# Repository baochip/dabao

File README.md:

# Dabao board design files

This repo contains the Kicad design files for the Dabao evaluation board for the Baochip-1x.

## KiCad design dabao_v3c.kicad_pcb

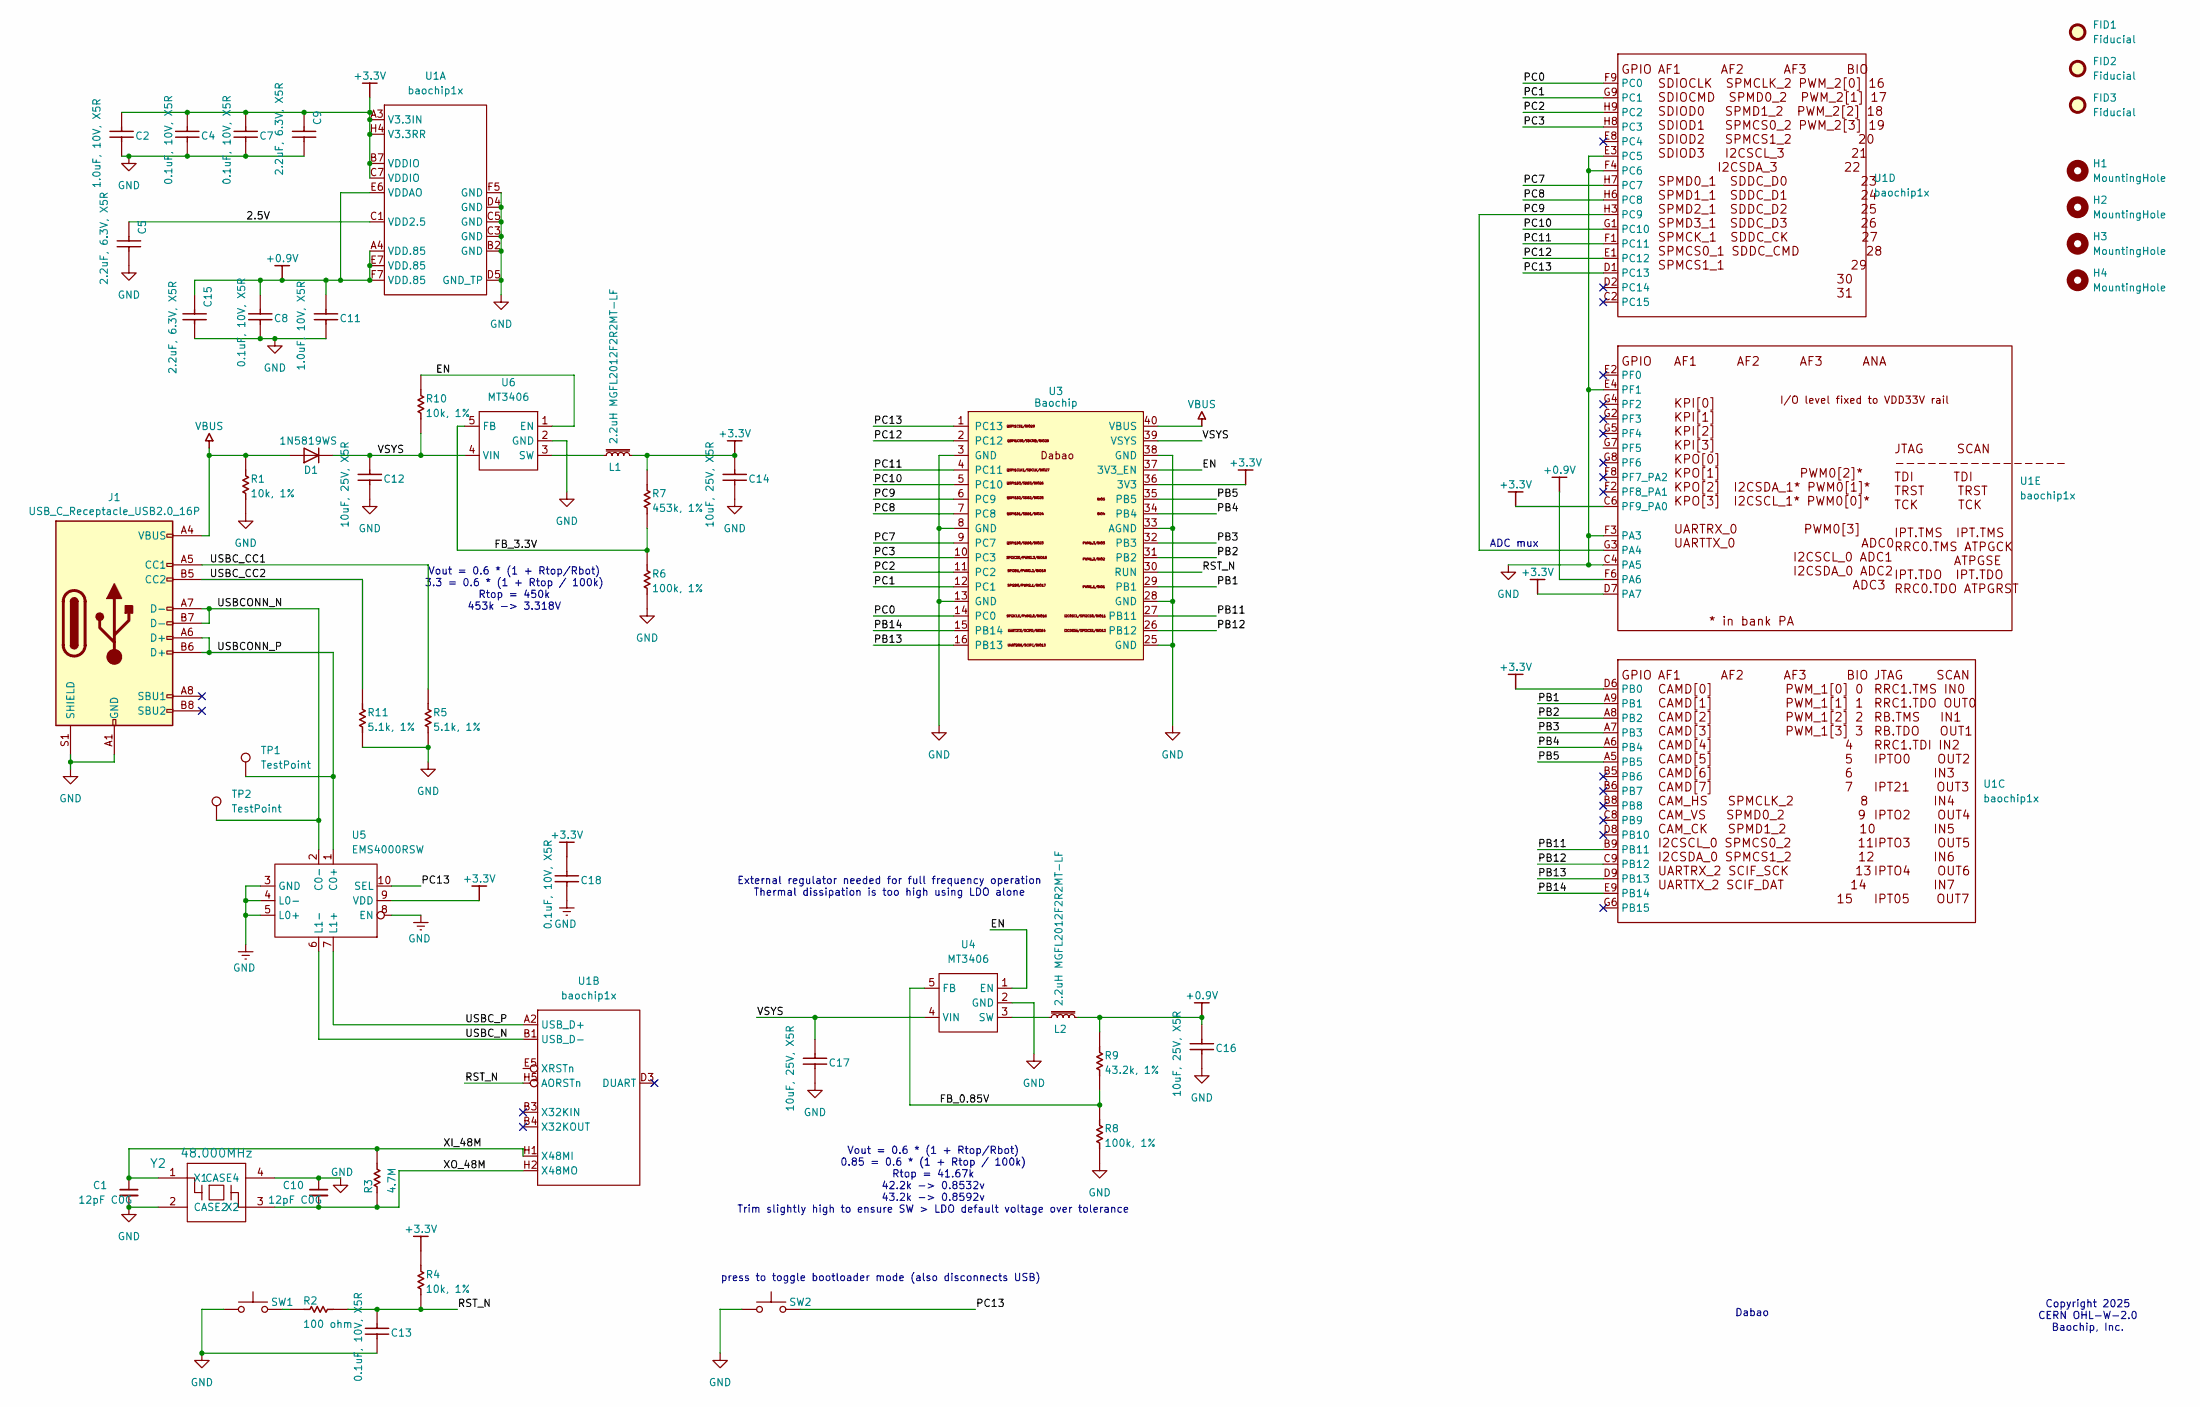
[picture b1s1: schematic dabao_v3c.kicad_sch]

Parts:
C1, C10: 12pF C0G; C_0201_0603Metric; Rating C0G 50V 0603; MPN CC0201JRNPO9BN120; LCSC C277478
C2, C11: 1.0uF, 10V, X5R; C_0201_0603Metric; MPN CL05A105KA5NQNC; LCSC C76935
C4, C7, C8, C13, C18: 0.1uF, 10V, X5R; C_0201_0603Metric; MPN CL05B104KO5NNNC; LCSC C76934
C5, C9, C15: 2.2uF, 6.3V, X5R; C_0201_0603Metric; MPN GRM033R60J225ME47D; LCSC C76933
C12, C14, C16, C17: 10uF, 25V, X5R; C_0603_1608Metric; MPN CL10A106MA8NRNC; LCSC C96446
D1: 1N5819WS; D_SOD-323; MPN SD103AWS; LCSC C191023
FID1, FID2: Fiducial; IRIS fiducial 0.4mm
FID3: Fiducial; IRIS fiducial2 0.4mm
H1, H2, H3, H4: MountingHole; MountingHole_2.2mm_M2_DIN965
J1: USB_C_Receptacle_USB2.0_16P; USB_C_Receptacle_HRO_TYPE-C-31-M-12; LCSC C165948
L1, L2: 2.2uH MGFL2012F2R2MT-LF; L_0805_2012Metric; LCSC C281115
R1, R4, R10: 10k, 1%; R_0201_0603Metric; MPN ANY; LCSC C106225
R2: 100 ohm; R_0402_1005Metric; MPN ANY; LCSC C106232
R3: 4.7M; R_0402_1005Metric; MPN ANY; LCSC C474132
R5, R11: 5.1k, 1%; R_0402_1005Metric; MPN ANY; LCSC C25905
R6, R8: 100k, 1%; R_0201_0603Metric; MPN ANY; LCSC C106224
R7: 453k, 1%; R_0201_0603Metric; MPN ANY; LCSC C423509
R9: 43.2k, 1%; R_0201_0603Metric; MPN ANY; LCSC C158519
SW1, SW2: SW_Push; SW_Push_1P1T_XKB_TS-1187A; MPN TS-1187A-B-B-B; LCSC C528026
TP1, TP2: TestPoint; TestPoint_Pad_D1.0mm
U1: baochip1x; WLCSP-71_9x8_4.062x3.762mm
U3: Baochip; Dabao_Vendor_Substrate
U4, U6: MT3406; SOT-23-5; LCSC C22462728
U5: EMS4000RSW; QFN-10_1.4x1.8_Pitch0.4mm; LCSC C49186227
Y2: 48.000MHz; Crystal_SMD_3225-4Pin_3.2x2.5mm; LCSC C2892060

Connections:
+0.9V: C8.1, C11.1, C15.1, C16.1, L2.2, R9.1, U1.A4 (VDD.85), U1.E6 (VDDAO), U1.E7 (VDD.85), U1.F6 (PA6), U1.F7 (VDD.85)
+3.3V: C2.1, C4.1, C7.1, C9.1, C14.1, C18.1, L1.2, R4.1, R7.1, U1.A3 (V3.3IN), U1.B7 (VDDIO), U1.C6 (PF9_PA0), U1.C7 (VDDIO), U1.D6 (PB0), U1.D7 (PA7), U1.H4 (V3.3RR), U3.36 (3V3), U5.9 (VDD)
/2.5V: C5.1, U1.C1 (VDD2.5)
/EN: R10.1, U3.37 (3V3_EN), U4.1 (EN), U6.1 (EN)
/FB_0.85V: R8.1, R9.2, U4.5 (FB)
/FB_3.3V: R6.1, R7.2, U6.5 (FB)
/PB1: U1.A9 (PB1), U3.29 (PB1)
/PB2: U1.A8 (PB2), U3.31 (PB2)
/PB3: U1.A7 (PB3), U3.32 (PB3)
/PB4: U1.A6 (PB4), U3.34 (PB4)
/PB5: U1.A5 (PB5), U3.35 (PB5)
/PB11: U1.B9 (PB11), U3.27 (PB11)
/PB12: U1.C9 (PB12), U3.26 (PB12)
/PB13: U1.D9 (PB13), U3.16 (PB13)
/PB14: U1.E9 (PB14), U3.15 (PB14)
/PC0: U1.F9 (PC0), U3.14 (PC0)
/PC1: U1.G9 (PC1), U3.12 (PC1)
/PC2: U1.H9 (PC2), U3.11 (PC2)
/PC3: U1.H8 (PC3), U3.10 (PC3)
/PC7: U1.H7 (PC7), U3.9 (PC7)
/PC8: U1.H6 (PC8), U3.7 (PC8)
/PC9: U1.G3 (PA4), U1.H3 (PC9), U3.6 (PC9)
/PC10: U1.G1 (PC10), U3.5 (PC10)
/PC11: U1.F1 (PC11), U3.4 (PC11)
/PC12: U1.E1 (PC12), U3.2 (PC12)
/PC13: SW2.2, U1.D1 (PC13), U3.1 (PC13), U5.10 (SEL)
/RST_N: C13.1, R2.2, R4.2, U1.H5 (AORSTn), U3.30 (RUN)
/USBCONN_N: J1.A7 (D-), J1.B7 (D-), TP2.1, U5.2 (C0-)
/USBCONN_P: J1.A6 (D+), J1.B6 (D+), TP1.1, U5.1 (C0+)
/USBC_CC1: J1.A5 (CC1), R5.2
/USBC_CC2: J1.B5 (CC2), R11.2
/USBC_N: U1.B1 (USB_D-), U5.6 (L1-)
/USBC_P: U1.A2 (USB_D+), U5.7 (L1+)
/VSYS: C12.1, C17.1, D1.1 (K), R10.2, U3.39 (VSYS), U4.4 (VIN), U6.4 (VIN)
/XI_48M: C1.1, R3.2, U1.H1 (X48MI), Y2.1 (X1)
/XO_48M: C10.2, R3.1, U1.H2 (X48MO), Y2.3 (X2)
GND: C1.2, C2.2, C4.2, C5.2, C7.2, C8.2, C9.2, C10.1, C11.2, C12.2, C13.2, C14.2, C15.2, C16.2, C17.2, C18.2, J1.A1 (GND), J1.A12 (GND), J1.B1 (GND), J1.B12 (GND), J1.S1 (SHIELD), R1.2, R5.1, R6.2, R8.2, R11.1, SW1.1, SW2.1, U1.B2 (GND), U1.C3 (GND), U1.C4 (PA5), U1.C5 (GND), U1.D4 (GND), U1.D5 (GND_TP), U1.E3 (PC5), U1.E4 (PF1), U1.F3 (PA3), U1.F4 (PC6), U1.F5 (GND), U3.3 (GND), U3.8 (GND), U3.13 (GND), U3.25 (GND), U3.28 (GND), U3.33 (AGND), U3.38 (GND), U4.2 (GND), U5.3 (GND), U5.4 (L0-), U5.5 (L0+), U5.8 (EN), U6.2 (GND), Y2.2 (CASE2), Y2.4 (CASE4)
unnamed: R2.1, SW1.2
unnamed: L2.1, U4.3 (SW)
unnamed: L1.1, U6.3 (SW)
VBUS: D1.2 (A), J1.A4 (VBUS), J1.A9 (VBUS), J1.B4 (VBUS), J1.B9 (VBUS), R1.1, U3.40 (VBUS)

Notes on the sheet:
Vout = 0.6 * (1 + Rtop/Rbot) 3.3 = 0.6 * (1 + Rtop / 100k) Rtop = 450k 453k -> 3.318V
ADC mux
External regulator needed for full frequency operation Thermal dissipation is too high using LDO alone
Copyright 2025 CERN OHL-W-2.0 Baochip, Inc.
Dabao
press to toggle bootloader mode (also disconnects USB)
Vout = 0.6 * (1 + Rtop/Rbot) 0.85 = 0.6 * (1 + Rtop / 100k) Rtop = 41.67k 42.2k -> 0.8532v 43.2k -> 0.8592v Trim slightly high to ensure SW > LDO default voltage over tolerance

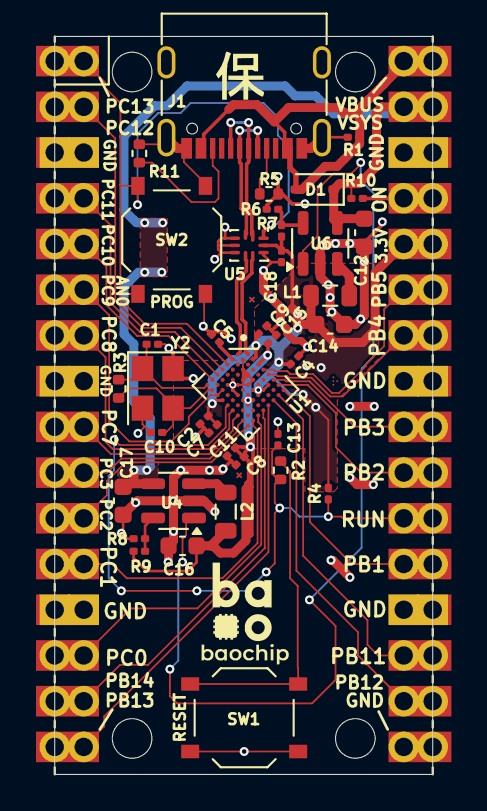
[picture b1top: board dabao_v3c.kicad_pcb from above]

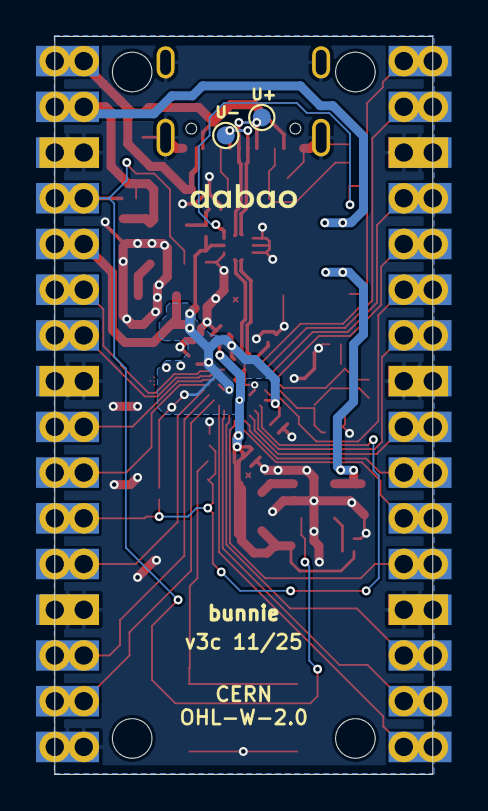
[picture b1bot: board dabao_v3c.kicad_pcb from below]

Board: 2 copper layers, 21.0 x 41.0 mm, 48 parts (2 on the bottom side), 41 nets.

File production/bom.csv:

Designator,Footprint,Quantity,Value,LCSC Part #
"C1, C10",0201,2,12pF C0G,C277478
"C11, C2",0201,2,"1.0uF, 10V, X5R",C76935
"C12, C14, C16, C17",0603,4,"10uF, 25V, X5R",C96446
"C13, C18, C4, C7, C8",0201,5,"0.1uF, 10V, X5R",C76934
"C15, C5, C9",0201,3,"2.2uF, 6.3V, X5R",C76933
D1,D_SOD-323,1,1N5819WS,C191023
J1,USB_C_Receptacle_HRO_TYPE-C-31-M-12,1,USB_C_Receptacle_USB2.0_16P,C165948
"L1, L2",0805,2,2.2uH MGFL2012F2R2MT-LF,C281115
"R1, R10, R4",0201,3,"10k, 1%",C106225
"R11, R5",0402,2,"5.1k, 1%",C25905
R2,0402,1,100 ohm,C106232
R3,0402,1,4.7M,C474132
"R6, R8",0201,2,"100k, 1%",C106224
R7,0201,1,"453k, 1%",C423509
R9,0201,1,"43.2k, 1%",C158519
"SW1, SW2",SW_Push_1P1T_XKB_TS-1187A,2,SW_Push,C528026
U1,WLCSP-71_9x8_4.062x3.762mm,1,baochip1x,
U3,Dabao_Vendor_Substrate,1,Baochip,
"U4, U6",SOT-23-5,2,MT3406,C22462728
U5,QFN-10_1.4x1.8_Pitch0.4mm,1,EMS4000RSW,C49186227
Y2,Crystal_SMD_3225-4Pin_3.2x2.5mm,1,48.000MHz,C2892060

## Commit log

2025-10-30 update v3b files
2025-11-04 add artifacts required for USB ID
2025-11-10 update to v3c
    fix USB-CC resistor issue and improve thermal/electrical
    performance on chip power pins
2025-11-10 remove old files
2025-11-10 update silkscreen and add step file
2025-11-17 update routing to latest rev
2025-11-17 add usb pads on the back side
    allows for pogo testing & also possibly SMT access to USB
    board designers will have to exercise caution tho - 480Mbps won't
    tolerate a lot of shenanigans in layout.
